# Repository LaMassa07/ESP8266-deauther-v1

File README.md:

# ESP8266 Deauther v1    
A compact WiFi gadget to perform a variety of actions to test 802.11 networks, using an ESP8266 board.

<br>

## 📌 Features
- **Scan** for WiFi networks and clients
- **Create** docents of WiFi networks (beacon flooding)
- **Confuse** WiFi trackers by sending fake probe requests (probe flooding)
- **Disconnect** selected devices by sending deauth packets (deauthentication attack)

<br>

## ⚙️ Setup
- First, be sure to have the <a href="https://www.arduino.cc/en/software/">Arduino IDE</a> at the last version

### Libraries
Go to `Sketch` → `Include Library` → `Manage Library` and install:
- **ArduinoJson** by *Benoit Blanchon* version 5.x.x
- **ESP8266 and ESP32 OLED driver for SSD1306 displays** by *ThingPulse*
### Board
Go to `File` → `Preferences` and add, in the Additional boards manager URLs field: 
```
https://arduino.esp8266.com/stable/package_esp8266com_index.json
```

Than, go to `Tools` → `Boards` → `Boards Manager` and install:
- **esp8266** by *ESP8266 Community*

<br>

## 🛠️ Installing the code
Open the *.ino* file with the IDE.
Before uploading it, go to the file called `A_config.h`. That is the file you can edit to change the pin settings. In particular, you can:
- **choose** the pins for buttons, led and display
- **adjust** the orentation of the display
- **change** the default SSID and PASSWORD for the web interface

<br>

When you are ready, click **Upload**

<br>

## 🔌 Build the circuit
### Materials:
- ESP8266 NodeMCU LoLin v3 board *(or similar, I only tested that board)*
- SSD1306 OLED display
- 4 x buttons
- 3 x 220Ω resistors
- led RGB *(in order to use my PCB, the led must be common K)*

### Schematic

<br>
<br>

## 🖥️ Use
> ⚠️ **USE THIS ONLY ON NETWORKS YOU OWN OR HAVE EXPLICIT PERMISSION TO TEST.**  
> This project is intended purely for *learning, debugging and local demonstrations* of Wi-Fi packet behavior

You can use the device in two ways:
- Using the buttons to scroll the displayed menu
- Using the web interface:
    - Connect you phone or pc to the network called `pwned` *(the default password is "deauther")*
    - In your web browser type `192.168.4.1`

<br>

## 🔋 More
Additionally, you can print the PCB, using the `PCB_Gerber.zip` folder, with some online services like <a href="https://jlcpcb.com/">JLPBC</a> or similar

<br>
<br>
<br>

## 🙌 Credits
Inspired by the work of <a href="https://github.com/spacehuhn">**@spacehuhn**</a>, creator of well-known Wi-Fi pentesting and deauther tools.
<br>
<br>

Find Me on:

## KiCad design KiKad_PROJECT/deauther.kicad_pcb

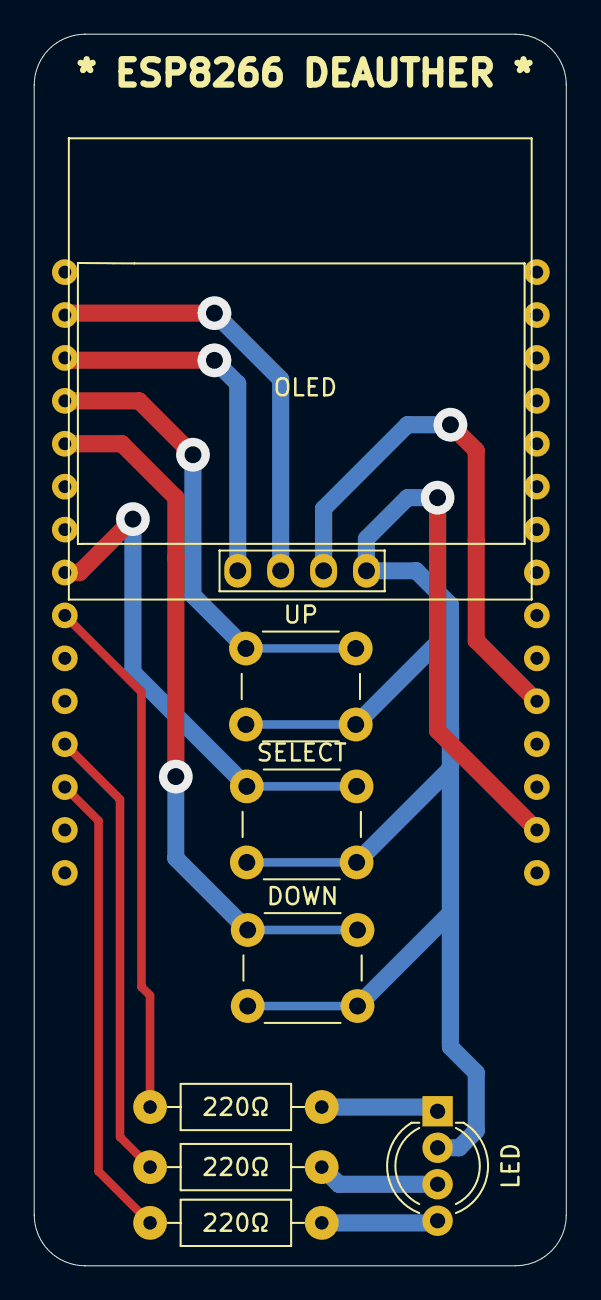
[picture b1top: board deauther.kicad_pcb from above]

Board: 2 copper layers, 31.5 x 72.9 mm, 9 parts (1 on the bottom side), 13 nets.

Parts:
220Ω, 220Ω#2, 220Ω#3: R_US; R_Axial_DIN0207_L6.3mm_D2.5mm_P10.16mm_Horizontal
DOWN: DOWN; SW_PUSH_6mm_H9.5mm
LED: LED_RKGB; LED_D5.0mm-4_RGB_Wide_Pins
OLED: OLED; 128x64OLED
SELECT: OK; SW_PUSH_6mm_H9.5mm
U1: NodeMCU1.0(ESP-12E); NodeMCU-LoLinV3
UP: UP; SW_PUSH_6mm_H9.5mm

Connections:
/B: 220Ω#3.2, U1.18 (TX(GPIO1))
/DOWN: DOWN.1, U1.26 (D4(GPIO2))
/G: 220Ω#2.2, U1.19 (RX(DPIO3))
/OK: SELECT.1, U1.23 (D5(GPIO14))
/R: 220Ω.2, U1.22 (D6(GPIO12))
/SCL: OLED.3, U1.29 (D1(GPIO5))
/SDA: OLED.4, U1.28 (D2(GPIO4))
/UP: U1.27 (D3(GPIO0)), UP.1
GND: DOWN.2, LED.2 (K), OLED.1, SELECT.2, U1.14 (GND), U1.17 (GND), U1.24 (GND), UP.2
unnamed: 220Ω#3.1, LED.4 (BA)
unnamed: 220Ω#2.1, LED.3 (GA)
unnamed: 220Ω.1, LED.1 (RA)
VCC: OLED.2, U1.11 (3.3V)

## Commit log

2025-12-09 first
2025-12-09 schematic
2025-12-10 Revise README for clarity and feature highlights
    Updated README to enhance clarity and add features section.
2025-12-10 Add GitHub badge to credits section
    Added GitHub badge link to README.
2025-12-12 Modify credits and add GitHub badge
    Updated credits section with a link to the creator's GitHub.
2025-12-12 Fix formatting in credits section of README
2026-01-15 Initial plan
2026-01-15 Refactor duplicated code: Extract common patterns into helper functions
    - Add template helper functions in functions.h
    - Refactor file path wrapper pattern in Names and SSIDs
    - Refactor selected() counting in Stations, Accesspoints, Names
    - Refactor selectAll/deselectAll in Stations and Names
    - Refactor MAC address finding in Stations and Names
2026-01-15 Refactor: Extract string matching pattern for select/deselect/remove
    - Add forEachMatching helper function
    - Refactor select/deselect/remove by string in Stations
    - Refactor select/deselect/remove by string in Accesspoints
2026-01-15 Fix: Refactor selectAll/deselectAll in Accesspoints to use helper function
    - Makes Accesspoints consistent with Stations and Names
    - Uses forEachItem helper with internal_select/internal_deselect
2026-01-15 Complete refactoring of duplicated code patterns
    Summary:
    - Added 5 reusable template helper functions
    - Refactored 21 methods across 4 classes
    - Net reduction: 73 deletions, 66 additions
    - Improved maintainability and consistency
